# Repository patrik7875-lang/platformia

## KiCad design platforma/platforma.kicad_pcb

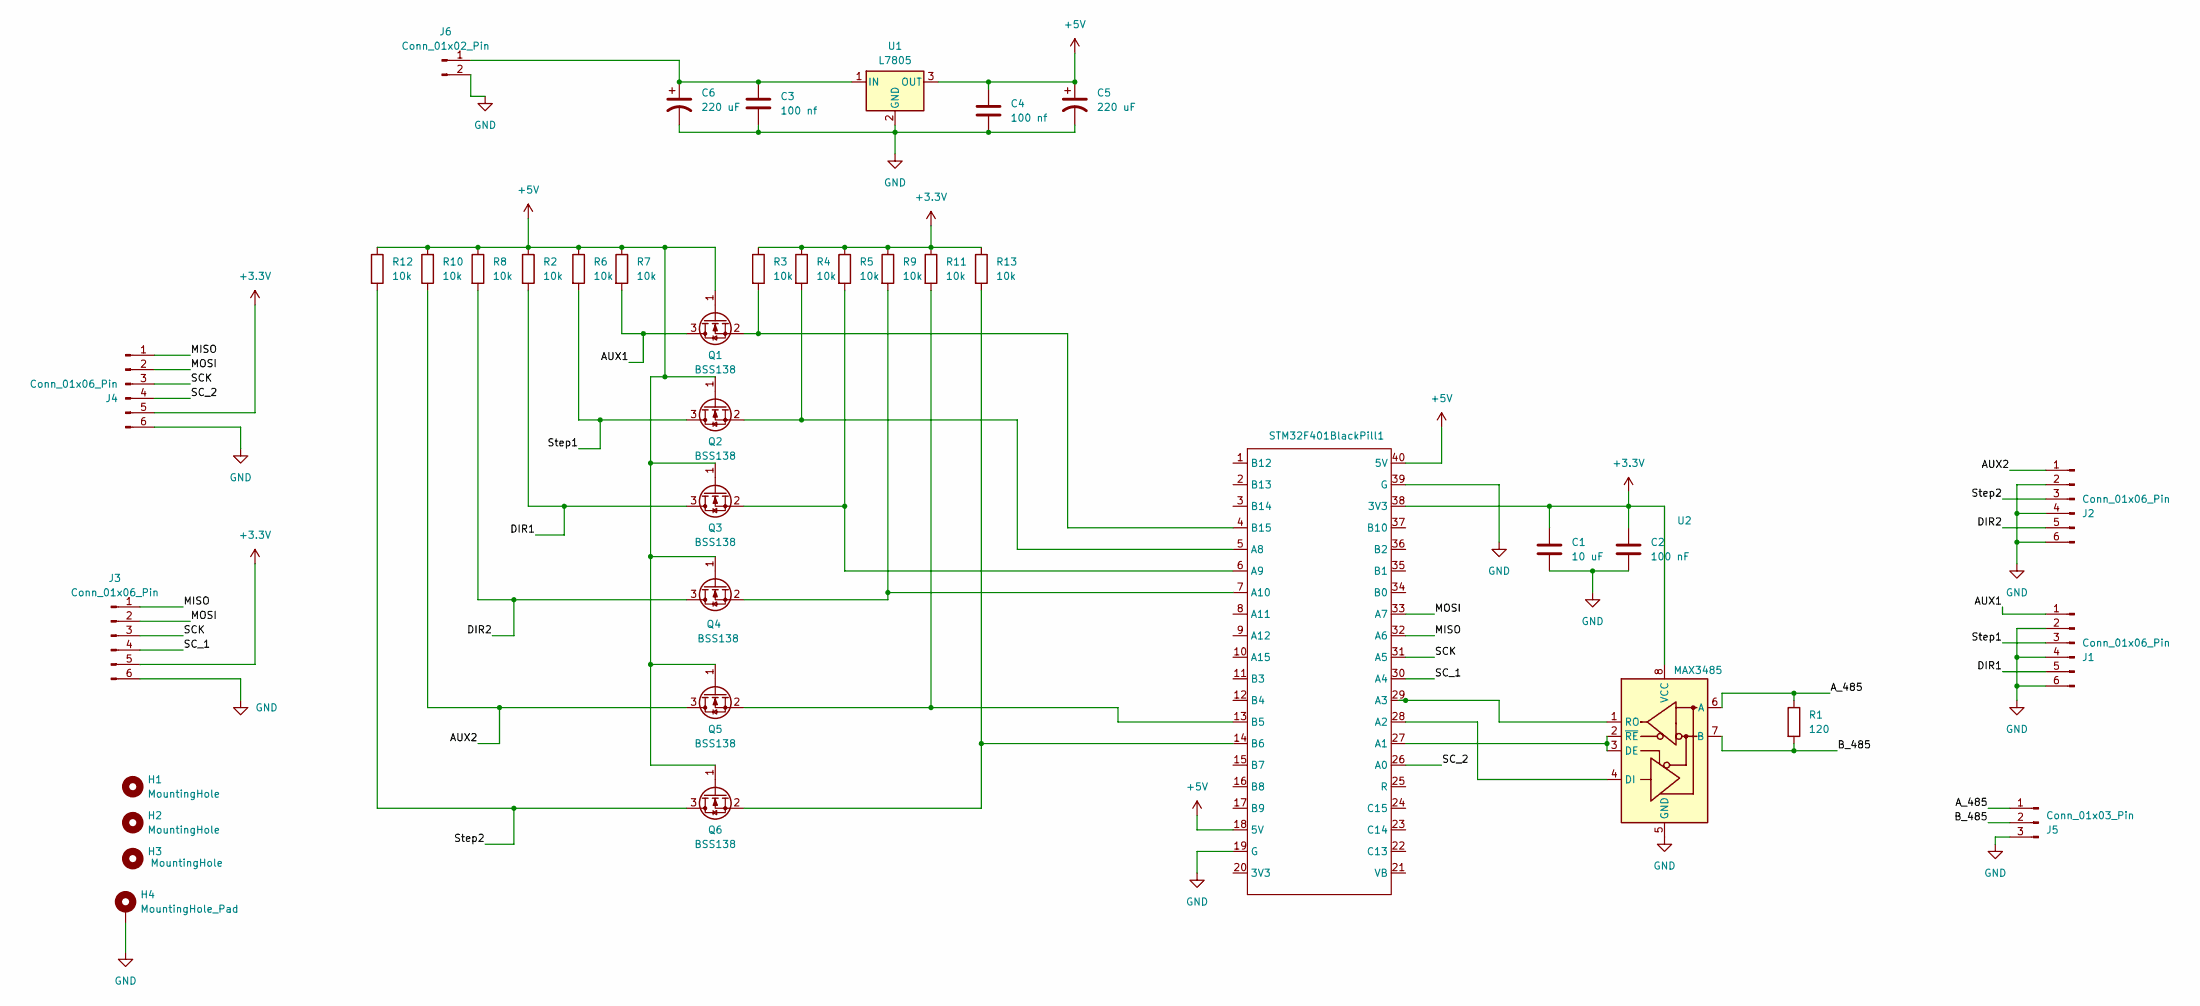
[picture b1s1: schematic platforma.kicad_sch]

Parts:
C1: 10 uF; C_1206_3216Metric
C2: 100 nF; C_1206_3216Metric
C3, C4: 100 nf; C_1206_3216Metric
C5, C6: 220 uF; CP_Radial_D8.0mm_P5.00mm
H1, H2, H3: MountingHole; MountingHole_3.2mm_M3_ISO7380
H4: MountingHole_Pad; MountingHole_3.2mm_M3_Pad
J1, J2, J3, J4: Conn_01x06_Pin; Molex_KK-254_AE-6410-06A_1x06_P2.54mm_Vertical
J5: Conn_01x03_Pin; Molex_KK-254_AE-6410-03A_1x03_P2.54mm_Vertical
J6: Conn_01x02_Pin; Molex_KK-254_AE-6410-02A_1x02_P2.54mm_Vertical
Q1, Q2, Q3, Q4, Q5, Q6: BSS138; SOT-23
R1: 120; R_1206_3216Metric
R2, R3, R4, R5, R6, R7, R8, R9, R10, R11, R12, R13: 10k; R_1206_3216Metric
STM32F401BlackPill1: DIP-40_W15.24mm_LongPads
U1: L7805; TO-263-2
U2: MAX3485; SOIC-8_3.9x4.9mm_P1.27mm

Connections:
+3.3V: C1.1, C2.1, J3.5, J4.5, R3.1, R4.1, R5.1, R9.1, R11.1, R13.1, STM32F401BlackPill1.38 (3V3), U2.8 (VCC)
+5V: C4.1, C5.1, Q1.1 (G), Q2.1 (G), Q3.1 (G), Q4.1 (G), Q5.1 (G), Q6.1 (G), R2.1, R6.1, R7.1, R8.1, R10.2, R12.1, STM32F401BlackPill1.18 (5V), STM32F401BlackPill1.40 (5V), U1.3 (OUT)
/AUX1: J1.1, Q1.3 (D), R7.2
/AUX2: J2.1, Q5.3 (D), R10.1
/A_485: J5.1, R1.1, U2.6 (A)
/B_485: J5.2, R1.2, U2.7 (B)
/DIR1: J1.5, Q3.3 (D), R2.2
/DIR2: J2.5, Q4.3 (D), R8.2
/MISO: J3.1, J4.1, STM32F401BlackPill1.32 (A6)
/MOSI: J3.2, J4.2, STM32F401BlackPill1.33 (A7)
/SCK: J3.3, J4.3, STM32F401BlackPill1.31 (A5)
/SC_1: J3.4, STM32F401BlackPill1.30 (A4)
/SC_2: J4.4, STM32F401BlackPill1.26 (A0)
/Step1: J1.3, Q2.3 (D), R6.2
/Step2: J2.3, Q6.3 (D), R12.2
GND: C1.2, C2.2, C3.2, C4.2, C5.2, C6.2, H4.1 (1_1), J1.2, J1.4, J1.6, J2.2, J2.4, J2.6, J3.6, J4.6, J5.3, J6.2, STM32F401BlackPill1.19 (G), STM32F401BlackPill1.39 (G), U1.2 (GND), U2.5 (GND)
unnamed: C3.1, C6.1, J6.1, U1.1 (IN)
unnamed: Q1.2 (S), R3.2, STM32F401BlackPill1.4 (B15)
unnamed: Q2.2 (S), R4.2, STM32F401BlackPill1.5 (A8)
unnamed: Q3.2 (S), R5.2, STM32F401BlackPill1.6 (A9)
unnamed: Q4.2 (S), R9.2, STM32F401BlackPill1.7 (A10)
unnamed: Q5.2 (S), R11.2, STM32F401BlackPill1.13 (B5)
unnamed: Q6.2 (S), R13.2, STM32F401BlackPill1.14 (B6)
unnamed: STM32F401BlackPill1.27 (A1), U2.2 (~RE), U2.3 (DE)
unnamed: STM32F401BlackPill1.28 (A2), U2.4 (DI)
unnamed: STM32F401BlackPill1.29 (A3), U2.1 (RO)

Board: 2 copper layers, 38 parts (18 on the bottom side), 26 nets, no tracks yet.
